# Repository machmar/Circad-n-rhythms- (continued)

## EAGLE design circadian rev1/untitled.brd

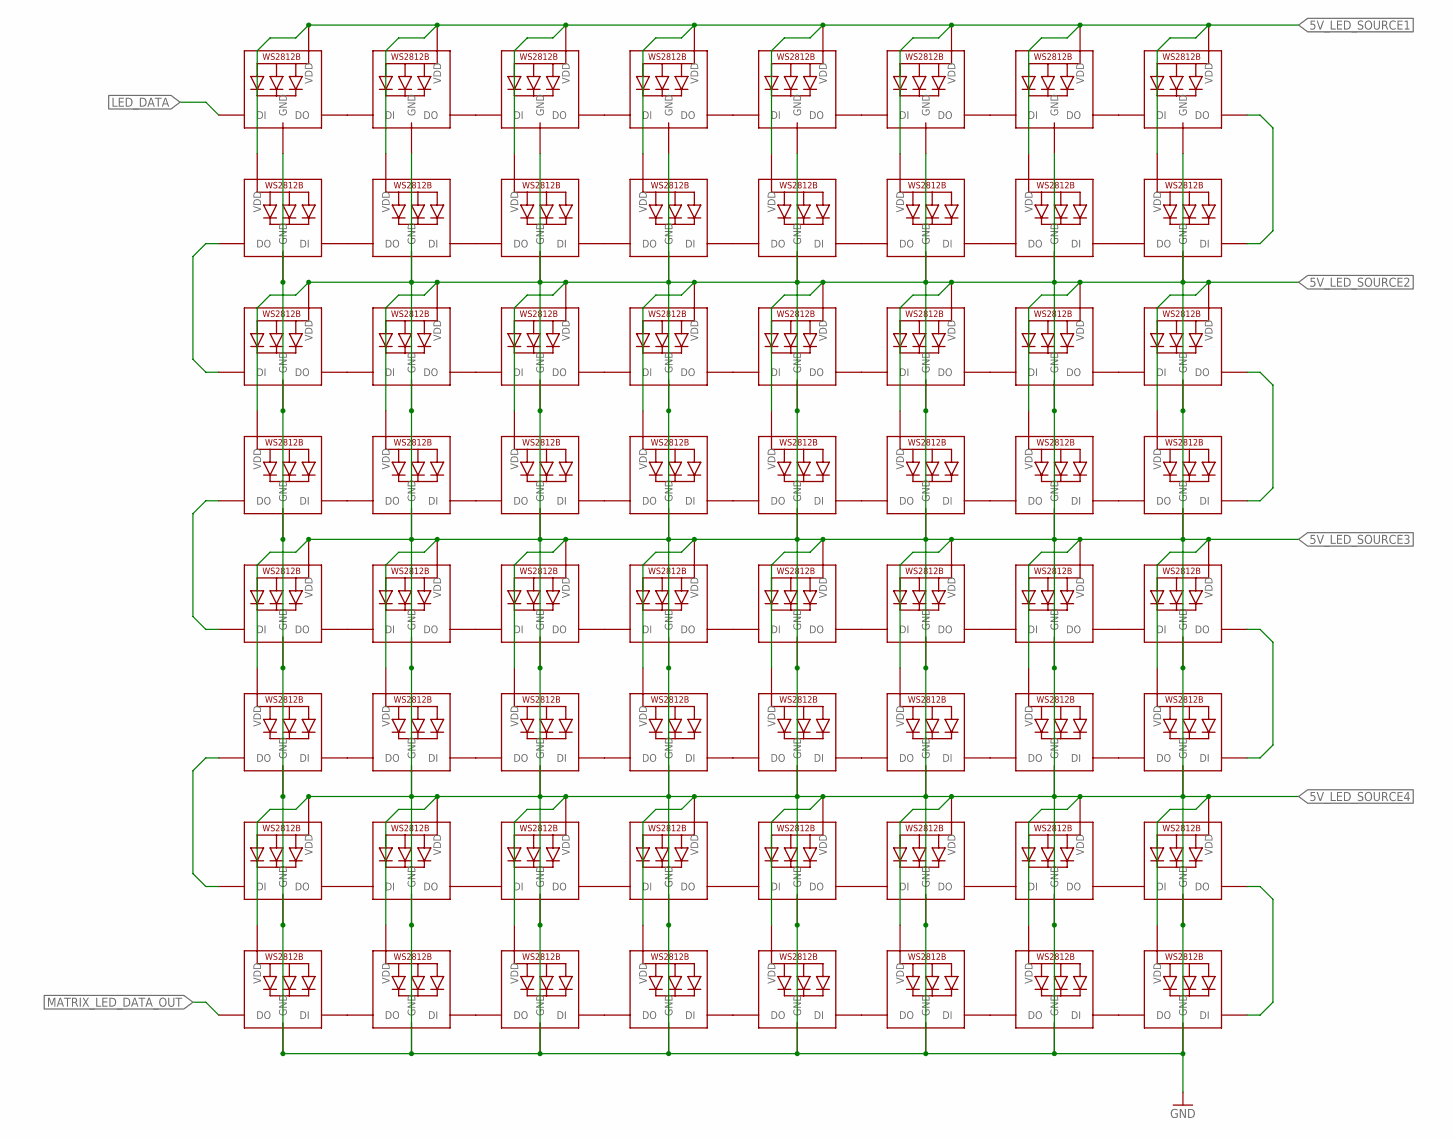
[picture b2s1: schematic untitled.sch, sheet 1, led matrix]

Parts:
LED1, LED2, LED3, LED4, LED5, LED6, LED7, LED8, LED9, LED10, LED11, LED12, LED13, LED14, LED15, LED16, LED17, LED18, LED19, LED20, LED21, LED22, LED23, LED24, LED25, LED26, LED27, LED28, LED29, LED30, LED31, LED32, LED33, LED34, LED35, LED36, LED37, LED38, LED39, LED40, LED41, LED42, LED43, LED44, LED45, LED46, LED47, LED48, LED49, LED50, LED51, LED52, LED53, LED54, LED55, LED56, LED57, LED58, LED59, LED60, LED61, LED62, LED63, LED64: WS2812B3535; LED3535

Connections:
5V_LED_SOURCE1: LED1.2 (VDD), LED2.2 (VDD), LED3.2 (VDD), LED4.2 (VDD), LED5.2 (VDD), LED6.2 (VDD), LED7.2 (VDD), LED8.2 (VDD), LED9.2 (VDD), LED10.2 (VDD), LED11.2 (VDD), LED12.2 (VDD), LED13.2 (VDD), LED14.2 (VDD), LED15.2 (VDD), LED16.2 (VDD); also elsewhere on the board
5V_LED_SOURCE2: LED17.2 (VDD), LED18.2 (VDD), LED19.2 (VDD), LED20.2 (VDD), LED21.2 (VDD), LED22.2 (VDD), LED23.2 (VDD), LED24.2 (VDD), LED25.2 (VDD), LED26.2 (VDD), LED27.2 (VDD), LED28.2 (VDD), LED29.2 (VDD), LED30.2 (VDD), LED31.2 (VDD), LED32.2 (VDD); also elsewhere on the board
5V_LED_SOURCE3: LED33.2 (VDD), LED34.2 (VDD), LED35.2 (VDD), LED36.2 (VDD), LED37.2 (VDD), LED38.2 (VDD), LED39.2 (VDD), LED40.2 (VDD), LED41.2 (VDD), LED42.2 (VDD), LED43.2 (VDD), LED44.2 (VDD), LED45.2 (VDD), LED46.2 (VDD), LED47.2 (VDD), LED48.2 (VDD); also elsewhere on the board
5V_LED_SOURCE4: LED49.2 (VDD), LED50.2 (VDD), LED51.2 (VDD), LED52.2 (VDD), LED53.2 (VDD), LED54.2 (VDD), LED55.2 (VDD), LED56.2 (VDD), LED57.2 (VDD), LED58.2 (VDD), LED59.2 (VDD), LED60.2 (VDD), LED61.2 (VDD), LED62.2 (VDD), LED63.2 (VDD), LED64.2 (VDD); also elsewhere on the board
GND: LED1.4 (GND), LED2.4 (GND), LED3.4 (GND), LED4.4 (GND), LED5.4 (GND), LED6.4 (GND), LED7.4 (GND), LED8.4 (GND), LED9.4 (GND), LED10.4 (GND), LED11.4 (GND), LED12.4 (GND), LED13.4 (GND), LED14.4 (GND), LED15.4 (GND), LED16.4 (GND), LED17.4 (GND), LED18.4 (GND), LED19.4 (GND), LED20.4 (GND), LED21.4 (GND), LED22.4 (GND), LED23.4 (GND), LED24.4 (GND), LED25.4 (GND), LED26.4 (GND), LED27.4 (GND), LED28.4 (GND), LED29.4 (GND), LED30.4 (GND), LED31.4 (GND), LED32.4 (GND), LED33.4 (GND), LED34.4 (GND), LED35.4 (GND), LED36.4 (GND), LED37.4 (GND), LED38.4 (GND), LED39.4 (GND), LED40.4 (GND), LED41.4 (GND), LED42.4 (GND), LED43.4 (GND), LED44.4 (GND), LED45.4 (GND), LED46.4 (GND), LED47.4 (GND), LED48.4 (GND), LED49.4 (GND), LED50.4 (GND), LED51.4 (GND), LED52.4 (GND), LED53.4 (GND), LED54.4 (GND), LED55.4 (GND), LED56.4 (GND), LED57.4 (GND), LED58.4 (GND), LED59.4 (GND), LED60.4 (GND), LED61.4 (GND), LED62.4 (GND), LED63.4 (GND), LED64.4 (GND); also elsewhere on the board
LED_DATA: LED1.1 (DI); also elsewhere on the board
MATRIX_LED_DATA_OUT: LED57.3 (DO); also elsewhere on the board
unnamed: LED9.1 (DI), LED10.3 (DO)
unnamed: LED10.1 (DI), LED11.3 (DO)
unnamed: LED11.1 (DI), LED12.3 (DO)
unnamed: LED12.1 (DI), LED13.3 (DO)
unnamed: LED13.1 (DI), LED14.3 (DO)
unnamed: LED14.1 (DI), LED15.3 (DO)
unnamed: LED15.1 (DI), LED16.3 (DO)
unnamed: LED25.1 (DI), LED26.3 (DO)
unnamed: LED26.1 (DI), LED27.3 (DO)
unnamed: LED27.1 (DI), LED28.3 (DO)
unnamed: LED28.1 (DI), LED29.3 (DO)
unnamed: LED29.1 (DI), LED30.3 (DO)
unnamed: LED30.1 (DI), LED31.3 (DO)
unnamed: LED31.1 (DI), LED32.3 (DO)
unnamed: LED41.1 (DI), LED42.3 (DO)
unnamed: LED42.1 (DI), LED43.3 (DO)
unnamed: LED43.1 (DI), LED44.3 (DO)
unnamed: LED44.1 (DI), LED45.3 (DO)
unnamed: LED45.1 (DI), LED46.3 (DO)
unnamed: LED46.1 (DI), LED47.3 (DO)
unnamed: LED47.1 (DI), LED48.3 (DO)
unnamed: LED1.3 (DO), LED2.1 (DI)
unnamed: LED2.3 (DO), LED3.1 (DI)
unnamed: LED3.3 (DO), LED4.1 (DI)
unnamed: LED4.3 (DO), LED5.1 (DI)
unnamed: LED5.3 (DO), LED6.1 (DI)
unnamed: LED6.3 (DO), LED7.1 (DI)
unnamed: LED7.3 (DO), LED8.1 (DI)
unnamed: LED57.1 (DI), LED58.3 (DO)
unnamed: LED24.3 (DO), LED32.1 (DI)
unnamed: LED40.3 (DO), LED48.1 (DI)
unnamed: LED56.3 (DO), LED64.1 (DI)
unnamed: LED41.3 (DO), LED49.1 (DI)
unnamed: LED25.3 (DO), LED33.1 (DI)
unnamed: LED9.3 (DO), LED17.1 (DI)
unnamed: LED58.1 (DI), LED59.3 (DO)
unnamed: LED59.1 (DI), LED60.3 (DO)
unnamed: LED60.1 (DI), LED61.3 (DO)
unnamed: LED61.1 (DI), LED62.3 (DO)
unnamed: LED62.1 (DI), LED63.3 (DO)
unnamed: LED63.1 (DI), LED64.3 (DO)
unnamed: LED17.3 (DO), LED18.1 (DI)
unnamed: LED18.3 (DO), LED19.1 (DI)
unnamed: LED19.3 (DO), LED20.1 (DI)
unnamed: LED20.3 (DO), LED21.1 (DI)
unnamed: LED21.3 (DO), LED22.1 (DI)
unnamed: LED22.3 (DO), LED23.1 (DI)
unnamed: LED23.3 (DO), LED24.1 (DI)
unnamed: LED33.3 (DO), LED34.1 (DI)
unnamed: LED34.3 (DO), LED35.1 (DI)
unnamed: LED35.3 (DO), LED36.1 (DI)
unnamed: LED36.3 (DO), LED37.1 (DI)
unnamed: LED37.3 (DO), LED38.1 (DI)
unnamed: LED38.3 (DO), LED39.1 (DI)
unnamed: LED39.3 (DO), LED40.1 (DI)
unnamed: LED49.3 (DO), LED50.1 (DI)
unnamed: LED50.3 (DO), LED51.1 (DI)
unnamed: LED51.3 (DO), LED52.1 (DI)
unnamed: LED52.3 (DO), LED53.1 (DI)
unnamed: LED53.3 (DO), LED54.1 (DI)
unnamed: LED54.3 (DO), LED55.1 (DI)
unnamed: LED55.3 (DO), LED56.1 (DI)
unnamed: LED8.3 (DO), LED16.1 (DI)

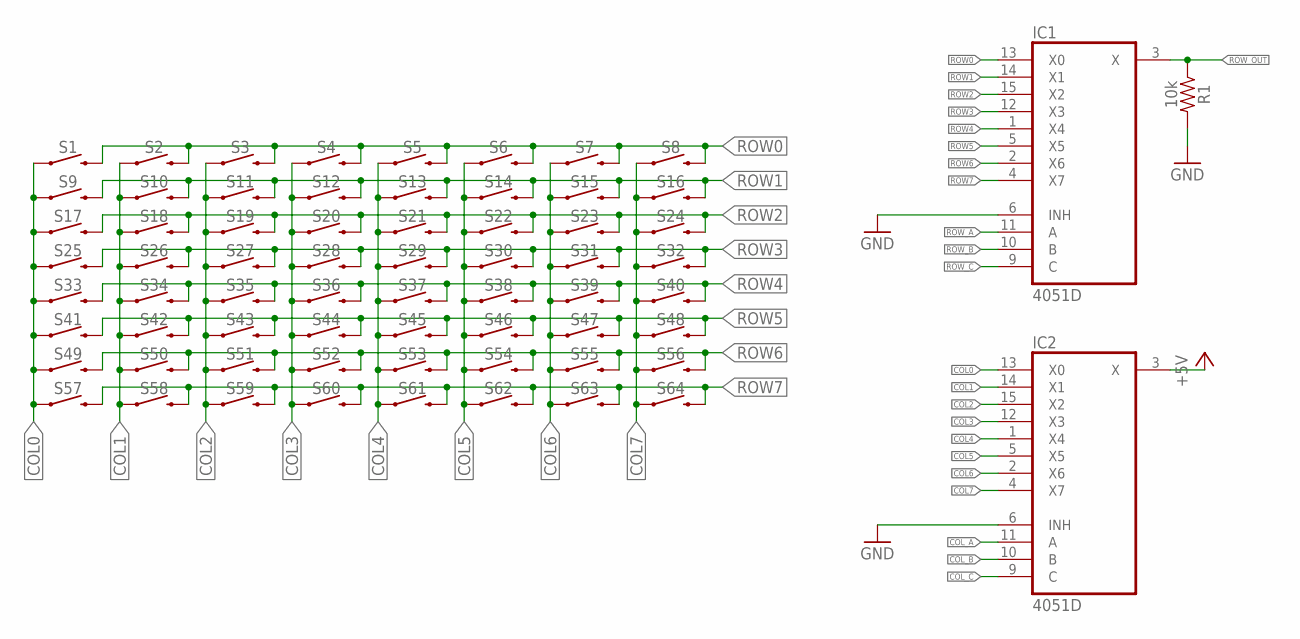
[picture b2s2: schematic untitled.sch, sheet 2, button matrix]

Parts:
IC1, IC2: 4051D; SO16
R1: 10k; 0603
S1, S2, S3, S4, S5, S6, S7, S8, S9, S10, S11, S12, S13, S14, S15, S16, S17, S18, S19, S20, S21, S22, S23, S24, S25, S26, S27, S28, S29, S30, S31, S32, S33, S34, S35, S36, S37, S38, S39, S40, S41, S42, S43, S44, S45, S46, S47, S48, S49, S50, S51, S52, S53, S54, S55, S56, S57, S58, S59, S60, S61, S62, S63, S64: MOMENTARY-SWITCH-SPST-SMD-6.0X3.5MM; TACTILE_SWITCH_SMD_6.0X3.5MM

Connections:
+5V: IC2.3 (X); also elsewhere on the board
COL0: IC2.13 (X0), S1.1, S9.1, S17.1, S25.1, S33.1, S41.1, S49.1, S57.1
COL1: IC2.14 (X1), S2.1, S10.1, S18.1, S26.1, S34.1, S42.1, S50.1, S58.1
COL2: IC2.15 (X2), S3.1, S11.1, S19.1, S27.1, S35.1, S43.1, S51.1, S59.1
COL3: IC2.12 (X3), S4.1, S12.1, S20.1, S28.1, S36.1, S44.1, S52.1, S60.1
COL4: IC2.1 (X4), S5.1, S13.1, S21.1, S29.1, S37.1, S45.1, S53.1, S61.1
COL5: IC2.5 (X5), S6.1, S14.1, S22.1, S30.1, S38.1, S46.1, S54.1, S62.1
COL6: IC2.2 (X6), S7.1, S15.1, S23.1, S31.1, S39.1, S47.1, S55.1, S63.1
COL7: IC2.4 (X7), S8.1, S16.1, S24.1, S32.1, S40.1, S48.1, S56.1, S64.1
COL_A: IC2.11 (A); also elsewhere on the board
COL_B: IC2.10 (B); also elsewhere on the board
COL_C: IC2.9 (C); also elsewhere on the board
GND: IC1.6 (INH), IC1.8 (GND), IC2.6 (INH), IC2.8 (GND), R1.2; also elsewhere on the board
ROW0: IC1.13 (X0), S1.2, S2.2, S3.2, S4.2, S5.2, S6.2, S7.2, S8.2
ROW1: IC1.14 (X1), S9.2, S10.2, S11.2, S12.2, S13.2, S14.2, S15.2, S16.2
ROW2: IC1.15 (X2), S17.2, S18.2, S19.2, S20.2, S21.2, S22.2, S23.2, S24.2
ROW3: IC1.12 (X3), S25.2, S26.2, S27.2, S28.2, S29.2, S30.2, S31.2, S32.2
ROW4: IC1.1 (X4), S33.2, S34.2, S35.2, S36.2, S37.2, S38.2, S39.2, S40.2
ROW5: IC1.5 (X5), S41.2, S42.2, S43.2, S44.2, S45.2, S46.2, S47.2, S48.2
ROW6: IC1.2 (X6), S49.2, S50.2, S51.2, S52.2, S53.2, S54.2, S55.2, S56.2
ROW7: IC1.4 (X7), S57.2, S58.2, S59.2, S60.2, S61.2, S62.2, S63.2, S64.2
ROW_A: IC1.11 (A); also elsewhere on the board
ROW_B: IC1.10 (B); also elsewhere on the board
ROW_C: IC1.9 (C); also elsewhere on the board
ROW_OUT: IC1.3 (X), R1.1; also elsewhere on the board
VCC: IC1.16 (VCC), IC2.16 (VCC); also elsewhere on the board
VEE: IC1.7 (VEE), IC2.7 (VEE); also elsewhere on the board

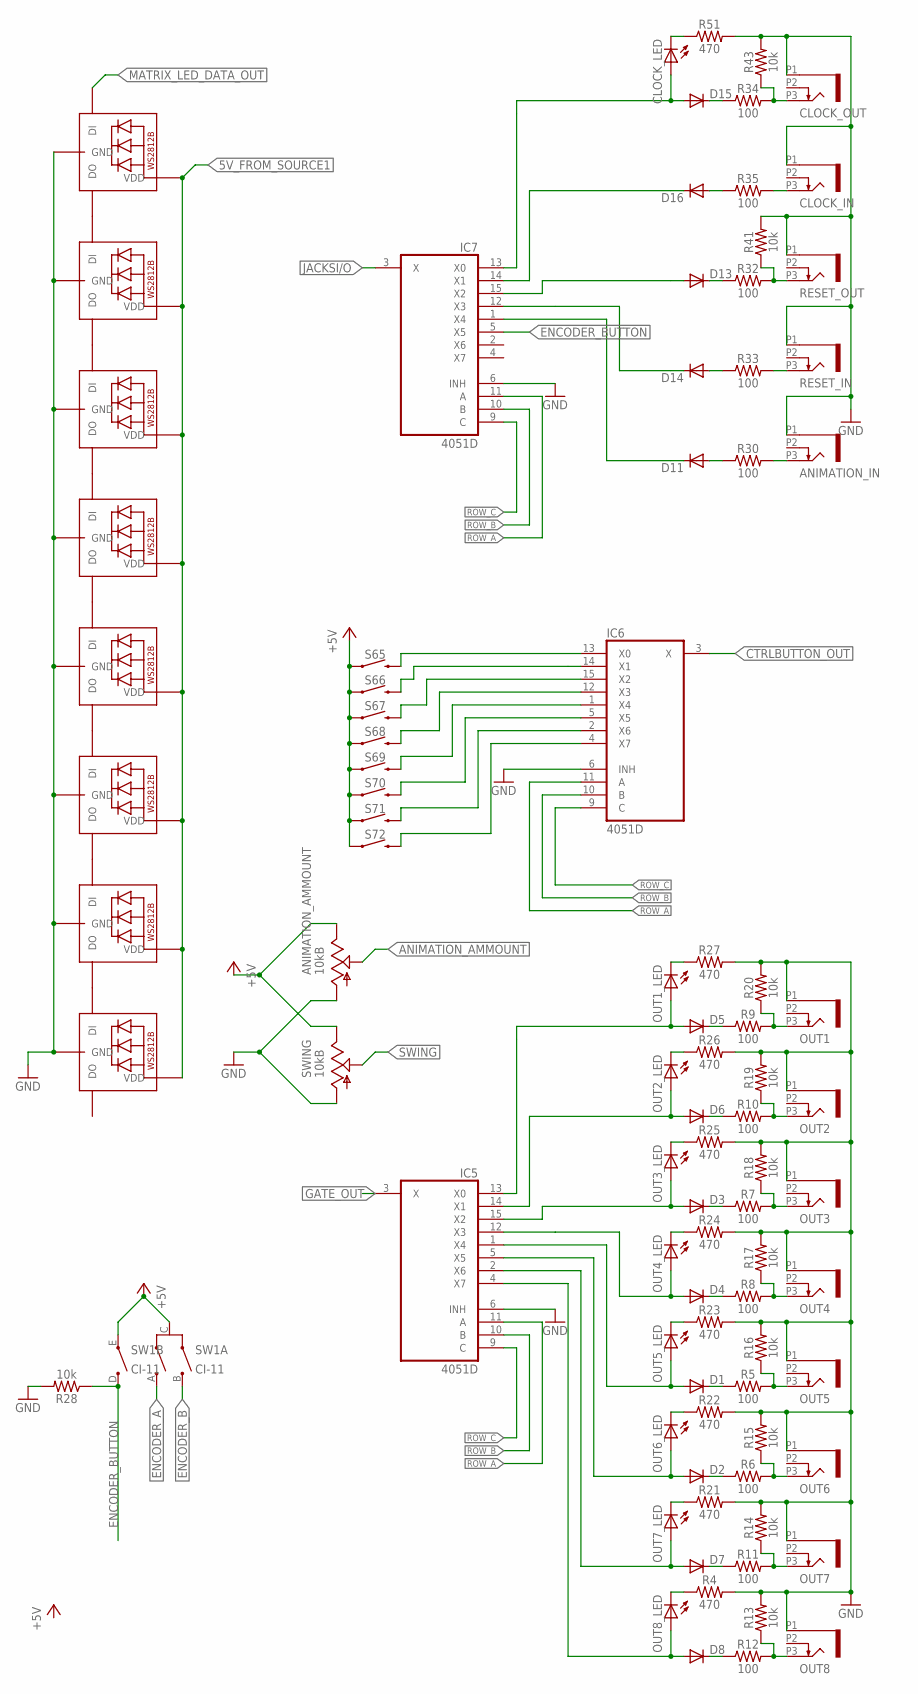
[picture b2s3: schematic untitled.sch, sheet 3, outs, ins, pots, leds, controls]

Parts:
ANIMATION_AMMOUNT: 10kB; ALPS_POT_VERTICAL
ANIMATION_IN: PJ301_THONKICONN8; WQP_PJ_301M8
CLOCK_IN: PJ301_THONKICONN1; WQP_PJ_301M1
CLOCK_LED: LED5MM
CLOCK_OUT: PJ301_THONKICONN1; WQP_PJ_301M1
D1, D2, D3, D4, D5, D6, D7, D8, D11, D13, D14, D15, D16: DIODE-DO214AC; DO214AC
IC5, IC6, IC7: 4051D; SO16
LED65, LED66, LED67, LED68, LED69, LED70, LED71, LED72: WS2812B3535; LED3535
OUT1, OUT2, OUT3, OUT4, OUT5, OUT6: PJ301_THONKICONN1; WQP_PJ_301M1
OUT1_LED, OUT2_LED, OUT3_LED, OUT4_LED, OUT5_LED, OUT6_LED, OUT7_LED, OUT8_LED: LED5MM
OUT7, OUT8: PJ301_THONKICONN8; WQP_PJ_301M8
R4, R21, R22, R23, R24, R25, R26, R27, R51: 470; 0603
R5, R6, R7, R8, R9, R10, R11, R12, R30, R32, R33, R34, R35: 100; 0603
R13, R14, R15, R16, R17, R18, R19, R20, R28, R41, R43: 10k; 0603
RESET_IN: PJ301_THONKICONN1; WQP_PJ_301M1
RESET_OUT: PJ301_THONKICONN8; WQP_PJ_301M8
S65, S66, S67, S68, S69, S70, S71, S72: MOMENTARY-SWITCH-SPST-SMD-6.0X3.5MM; TACTILE_SWITCH_SMD_6.0X3.5MM
SW1: CI-11
SWING: 10kB; ALPS_POT_VERTICAL

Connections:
5V_FROM_SOURCE1: LED65.2 (VDD), LED66.2 (VDD), LED67.2 (VDD), LED68.2 (VDD), LED69.2 (VDD), LED70.2 (VDD), LED71.2 (VDD), LED72.2 (VDD); also elsewhere on the board
+5V: ANIMATION_AMMOUNT.P$1 (E), S65.1, S66.1, S67.1, S68.1, S69.1, S70.1, S71.1, S72.1, SW1.C, SW1.E, SWING.P$1 (E); also elsewhere on the board
ANIMATION_AMMOUNT: ANIMATION_AMMOUNT.P$2 (S); also elsewhere on the board
CTRLBUTTON_OUT: IC6.3 (X); also elsewhere on the board
ENCODER_A: SW1.A; also elsewhere on the board
ENCODER_B: SW1.B; also elsewhere on the board
ENCODER_BUTTON: IC7.5 (X5), R28.1, SW1.D
GATE_OUT: IC5.3 (X); also elsewhere on the board
GND: ANIMATION_AMMOUNT.P$3 (A), ANIMATION_IN.P1 (1), CLOCK_IN.P1 (1), CLOCK_OUT.P1 (1), IC5.6 (INH), IC5.8 (GND), IC6.6 (INH), IC6.8 (GND), IC7.6 (INH), IC7.8 (GND), LED65.4 (GND), LED66.4 (GND), LED67.4 (GND), LED68.4 (GND), LED69.4 (GND), LED70.4 (GND), LED71.4 (GND), LED72.4 (GND), OUT1.P1 (1), OUT2.P1 (1), OUT3.P1 (1), OUT4.P1 (1), OUT5.P1 (1), OUT6.P1 (1), OUT7.P1 (1), OUT8.P1 (1), R4.2, R13.2, R14.2, R15.2, R16.2, R17.2, R18.2, R19.2, R20.2, R21.2, R22.2, R23.2, R24.2, R25.2, R26.2, R27.2, R28.2, R41.2, R43.2, R51.2, RESET_IN.P1 (1), RESET_OUT.P1 (1), SWING.P$3 (A); also elsewhere on the board
JACKSI/O: IC7.3 (X); also elsewhere on the board
MATRIX_LED_DATA_OUT: LED72.1 (DI); also elsewhere on the board
unnamed: D1.C, R5.1
unnamed: D2.C, R6.1
unnamed: OUT6.P3 (3), R6.2, R15.1
unnamed: OUT5.P3 (3), R5.2, R16.1
unnamed: D3.C, R7.1
unnamed: D4.C, R8.1
unnamed: D7.C, R11.1
unnamed: D8.C, R12.1
unnamed: OUT8.P3 (3), R12.2, R13.1
unnamed: OUT7.P3 (3), R11.2, R14.1
unnamed: OUT4.P3 (3), R8.2, R17.1
unnamed: OUT3.P3 (3), R7.2, R18.1
unnamed: D5.C, R9.1
unnamed: D6.C, R10.1
unnamed: OUT2.P3 (3), R10.2, R19.1
unnamed: OUT1.P3 (3), R9.2, R20.1
unnamed: D5.A, IC5.13 (X0), OUT1_LED.A
unnamed: D6.A, IC5.14 (X1), OUT2_LED.A
unnamed: D3.A, IC5.15 (X2), OUT3_LED.A
unnamed: D4.A, IC5.12 (X3), OUT4_LED.A
unnamed: D1.A, IC5.1 (X4), OUT5_LED.A
unnamed: D2.A, IC5.5 (X5), OUT6_LED.A
unnamed: D7.A, IC5.2 (X6), OUT7_LED.A
unnamed: D8.A, IC5.4 (X7), OUT8_LED.A
unnamed: LED65.3 (DO), LED66.1 (DI)
unnamed: LED65.1 (DI), LED70.3 (DO)
unnamed: LED66.3 (DO), LED67.1 (DI)
unnamed: LED67.3 (DO), LED68.1 (DI)
unnamed: LED68.3 (DO), LED69.1 (DI)
unnamed: LED69.3 (DO), LED71.1 (DI)
unnamed: LED70.1 (DI), LED72.3 (DO)
unnamed: OUT1_LED.K (C), R27.1
unnamed: OUT2_LED.K (C), R26.1
unnamed: OUT3_LED.K (C), R25.1
unnamed: OUT4_LED.K (C), R24.1
unnamed: OUT5_LED.K (C), R23.1
unnamed: OUT6_LED.K (C), R22.1
unnamed: OUT7_LED.K (C), R21.1
unnamed: OUT8_LED.K (C), R4.1
unnamed: D16.A, R35.1
unnamed: D14.A, R33.1
unnamed: D11.A, R30.1
unnamed: ANIMATION_IN.P3 (3), R30.2
unnamed: D13.C, R32.1
unnamed: R33.2, RESET_IN.P3 (3)
unnamed: R32.2, R41.1, RESET_OUT.P3 (3)
unnamed: D15.C, R34.1
unnamed: CLOCK_IN.P3 (3), R35.2
unnamed: CLOCK_OUT.P3 (3), R34.2, R43.1
unnamed: CLOCK_LED.A, D15.A, IC7.13 (X0)
unnamed: D16.C, IC7.14 (X1)
unnamed: D13.A, IC7.15 (X2)
unnamed: D14.C, IC7.12 (X3)
unnamed: D11.C, IC7.1 (X4)
unnamed: CLOCK_LED.K (C), R51.1
ROW8: IC6.13 (X0), S65.2
ROW9: IC6.14 (X1), S66.2
ROW10: IC6.15 (X2), S67.2
ROW11: IC6.12 (X3), S68.2
ROW12: IC6.1 (X4), S69.2
ROW13: IC6.5 (X5), S70.2
ROW14: IC6.2 (X6), S71.2
ROW15: IC6.4 (X7), S72.2
ROW_A: IC5.11 (A), IC6.11 (A), IC7.11 (A); also elsewhere on the board
ROW_B: IC5.10 (B), IC6.10 (B), IC7.10 (B); also elsewhere on the board
ROW_C: IC5.9 (C), IC6.9 (C), IC7.9 (C); also elsewhere on the board
SWING: SWING.P$2 (S); also elsewhere on the board
VCC: IC5.16 (VCC), IC6.16 (VCC), IC7.16 (VCC); also elsewhere on the board
VEE: IC5.7 (VEE), IC6.7 (VEE), IC7.7 (VEE); also elsewhere on the board

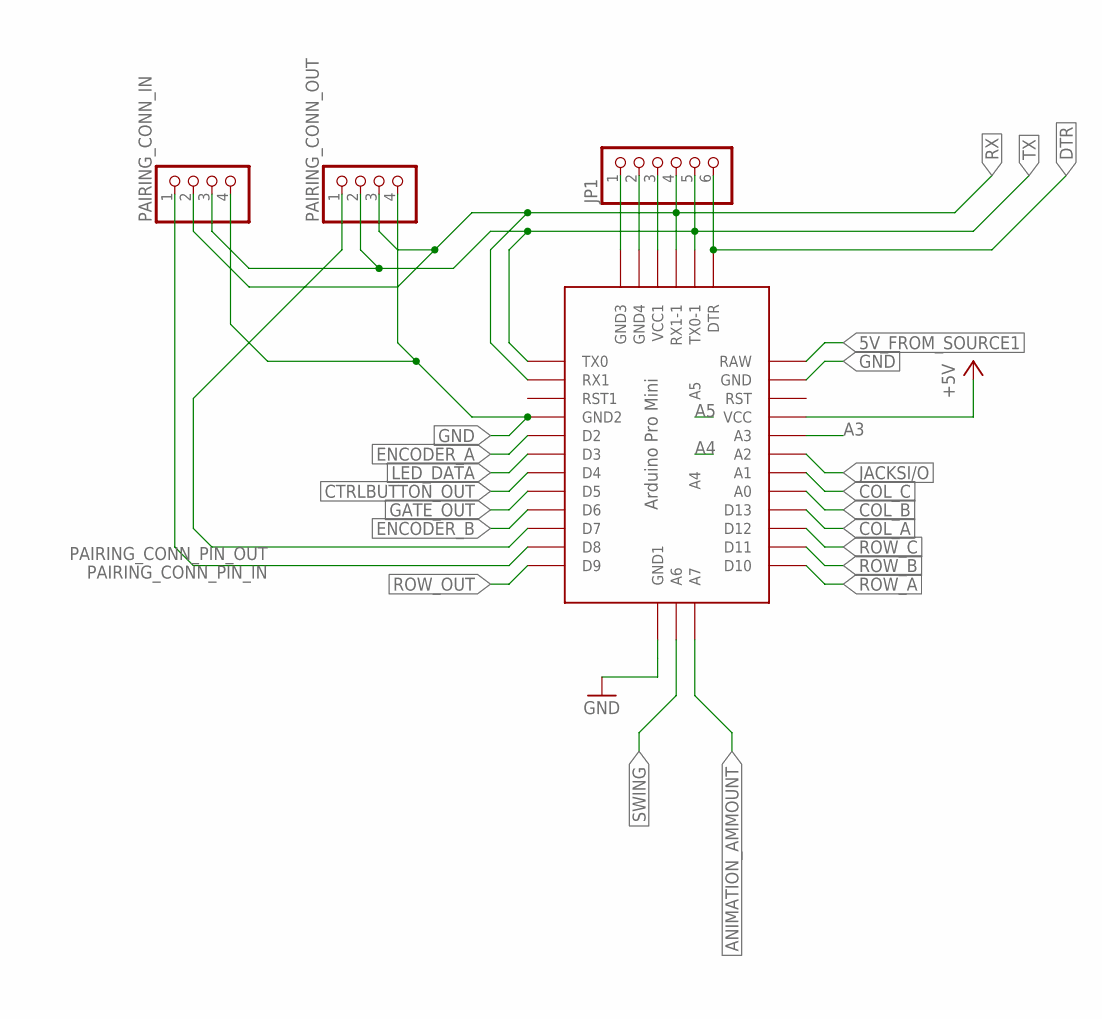
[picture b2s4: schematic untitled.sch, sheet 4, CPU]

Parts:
JP1: PINHD-1X6; 1X06
PAIRING_CONN_IN: PINHD-1X4; 1X04
PAIRING_CONN_OUT: PINHD-1X4; 1X04
U$1: ABK-PRO-MINI

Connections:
5V_FROM_SOURCE1: U$1.RAW; also elsewhere on the board
+5V: JP1.3, U$1.VCC, U$1.VCC1; also elsewhere on the board
A3: U$1.A3
A4: U$1.A4
A5: U$1.A5
ANIMATION_AMMOUNT: U$1.A7; also elsewhere on the board
COL_A: U$1.D13; also elsewhere on the board
COL_B: U$1.A0; also elsewhere on the board
COL_C: U$1.A1; also elsewhere on the board
CTRLBUTTON_OUT: U$1.D4; also elsewhere on the board
DTR: JP1.6, U$1.DTR; also elsewhere on the board
ENCODER_A: U$1.D2; also elsewhere on the board
ENCODER_B: U$1.D6; also elsewhere on the board
GATE_OUT: U$1.D5; also elsewhere on the board
GND: JP1.1, JP1.2, PAIRING_CONN_IN.4, PAIRING_CONN_OUT.4, U$1.GND, U$1.GND1 (GND2), U$1.GND2 (GND3), U$1.GND3 (GND4), U$1.GND4 (GND1); also elsewhere on the board
JACKSI/O: U$1.A2; also elsewhere on the board
LED_DATA: U$1.D3; also elsewhere on the board
PAIRING_CONN_PIN_IN: PAIRING_CONN_IN.1, U$1.D8
PAIRING_CONN_PIN_OUT: PAIRING_CONN_OUT.1, U$1.D7
ROW_A: U$1.D10; also elsewhere on the board
ROW_B: U$1.D11; also elsewhere on the board
ROW_C: U$1.D12; also elsewhere on the board
ROW_OUT: U$1.D9; also elsewhere on the board
RX: JP1.4, PAIRING_CONN_IN.2, PAIRING_CONN_OUT.3, U$1.RX1, U$1.RX1-1; also elsewhere on the board
SWING: U$1.A6; also elsewhere on the board
TX: JP1.5, PAIRING_CONN_IN.3, PAIRING_CONN_OUT.2, U$1.TX0, U$1.TX0-1; also elsewhere on the board

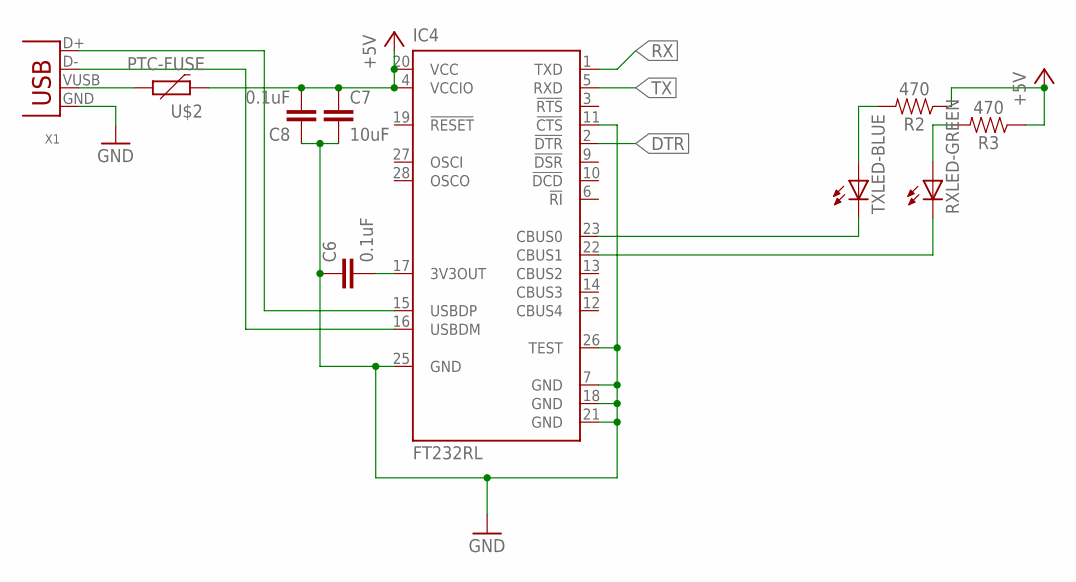
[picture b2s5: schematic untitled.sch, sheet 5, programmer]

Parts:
C6, C8: 0.1uF; 0603
C7: 10uF; 0603
IC4: FT232RL; SSOP28
R2, R3: 470; 0603
RXLED-GREEN: LEDCHIP-LED0603; CHIP-LED0603
TXLED-BLUE: LEDCHIP-LED0603; CHIP-LED0603
U$2: PTC-FUSE; 1206
X1: USB-B-S; USB-B-SMT

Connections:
+5V: C7.1, C8.2, IC4.4 (VCCIO), IC4.20 (VCC), R2.1, R3.1, U$2.1; also elsewhere on the board
DTR: IC4.2 (!DTR); also elsewhere on the board
GND: C6.1, C7.2, C8.1, IC4.7 (GND), IC4.11 (!CTS), IC4.18 (GND), IC4.21 (GND), IC4.25 (GND), IC4.26 (TEST), X1.GND; also elsewhere on the board
unnamed: R2.2, TXLED-BLUE.A
unnamed: R3.2, RXLED-GREEN.A
unnamed: U$2.2, X1.VUSB (VBUS)
unnamed: IC4.23 (CBUS0), TXLED-BLUE.C
unnamed: IC4.22 (CBUS1), RXLED-GREEN.C
unnamed: IC4.15 (USBDP), X1.D+
unnamed: IC4.16 (USBDM), X1.D-
unnamed: C6.2, IC4.17 (3V3OUT)
RX: IC4.1 (TXD); also elsewhere on the board
TX: IC4.5 (RXD); also elsewhere on the board

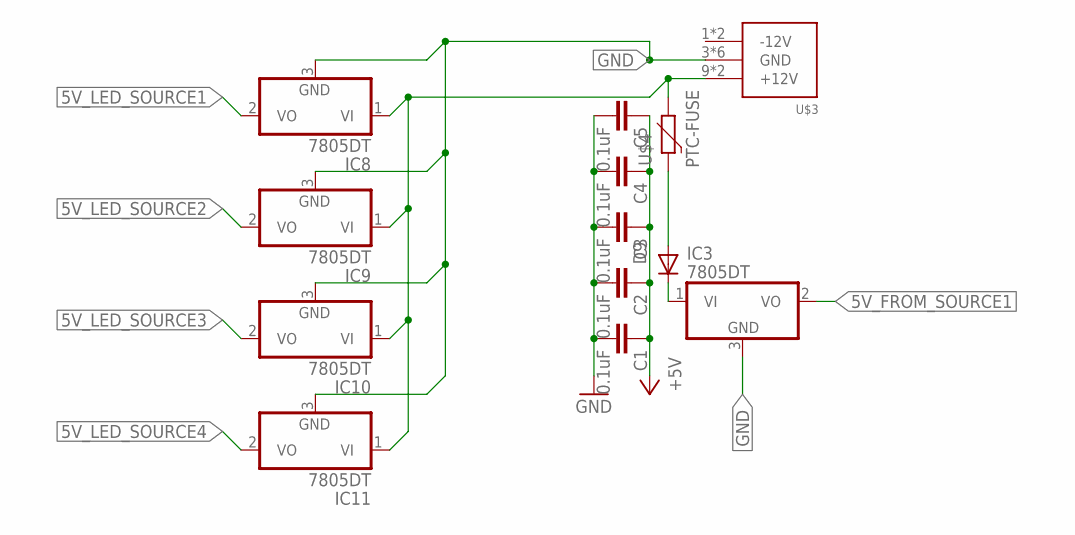
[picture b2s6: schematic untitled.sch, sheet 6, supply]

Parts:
C1, C2, C3, C4, C5: 0.1uF; 0603
D9: 1N5819HW; SOD123
IC3, IC8, IC9, IC10, IC11: 7805DT; TO252
U$3: POWER_SIMPLE10; POWER_10
U$4: PTC-FUSE; 1206

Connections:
5V_FROM_SOURCE1: IC3.2 (VO); also elsewhere on the board
5V_LED_SOURCE1: IC8.2 (VO); also elsewhere on the board
5V_LED_SOURCE2: IC9.2 (VO); also elsewhere on the board
5V_LED_SOURCE3: IC10.2 (VO); also elsewhere on the board
5V_LED_SOURCE4: IC11.2 (VO); also elsewhere on the board
+5V: C1.1, C2.1, C3.1, C4.1, C5.1; also elsewhere on the board
GND: C1.2, C2.2, C3.2, C4.2, C5.2, IC3.3 (GND), IC8.3 (GND), IC9.3 (GND), IC10.3 (GND), IC11.3 (GND), U$3.3 (GND), U$3.4 (GND), U$3.5 (GND), U$3.6 (GND), U$3.7 (GND), U$3.8 (GND); also elsewhere on the board
unnamed: IC8.1 (VI), IC9.1 (VI), IC10.1 (VI), IC11.1 (VI), U$3.9 (+12V), U$3.10 (+12V), U$4.2
unnamed: D9.A, U$4.1
unnamed: D9.C, IC3.1 (VI)

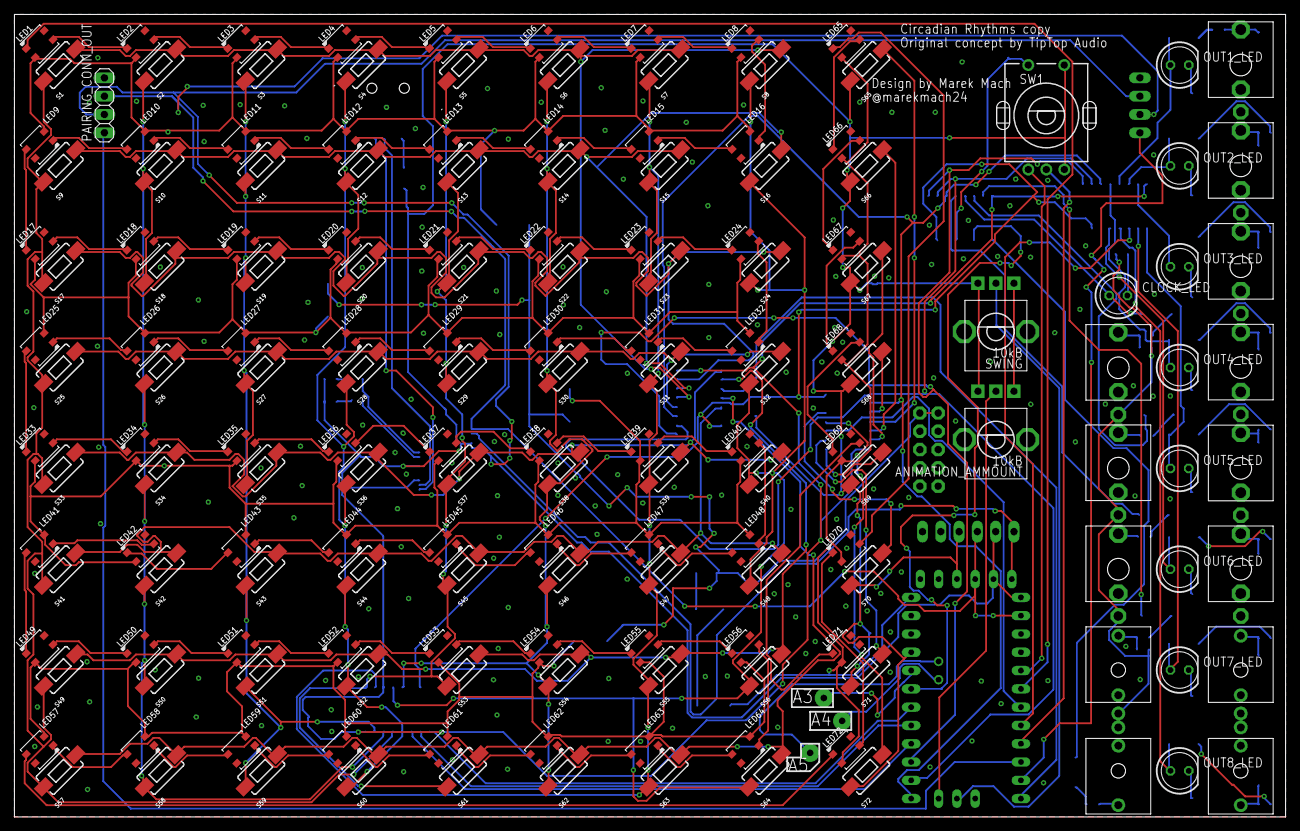
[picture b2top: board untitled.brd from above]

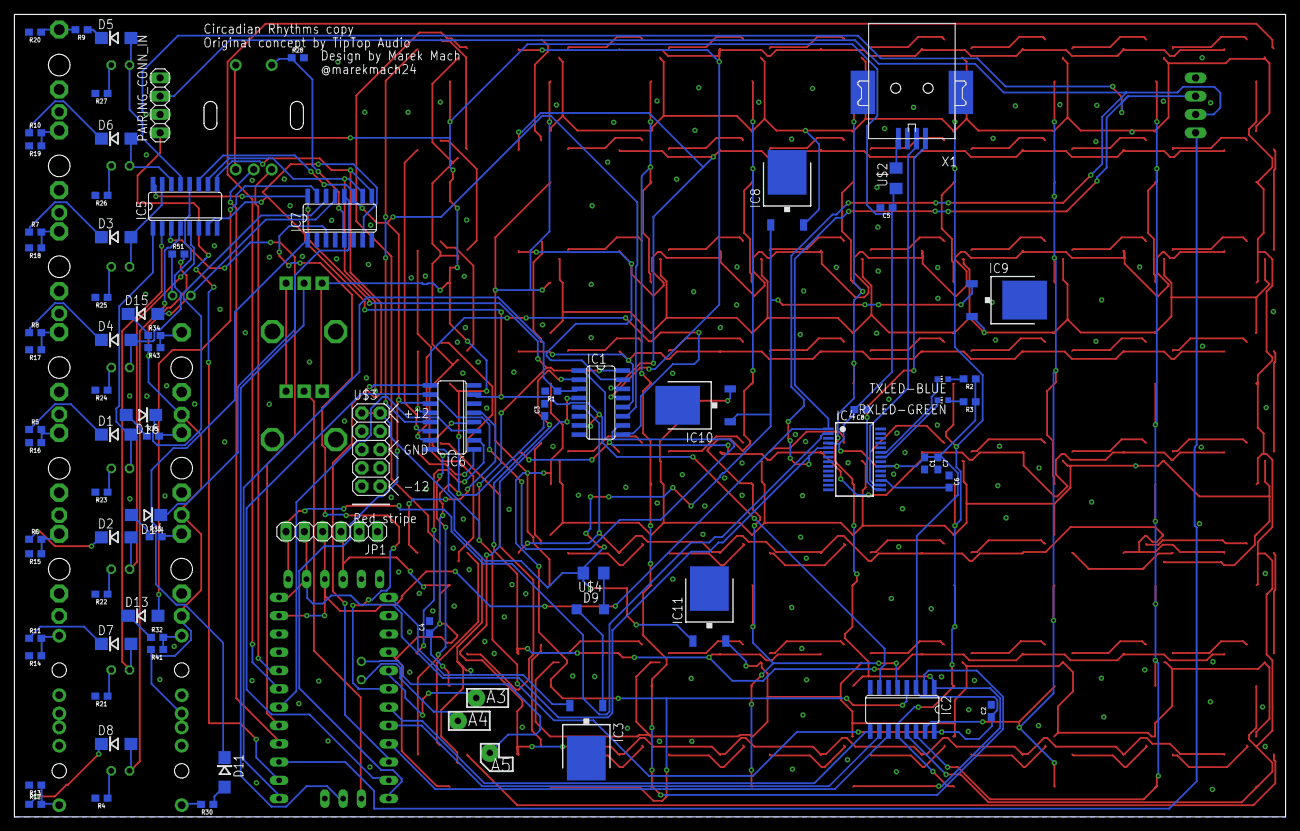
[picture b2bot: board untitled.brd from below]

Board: 2 copper layers, 176.5 x 111.4 mm, 248 parts (78 on the bottom side), 184 nets.

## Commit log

2018-12-15 The pcb and schematic
2019-07-30 it works now
    kinda
2019-07-30 code works now
    use the rev2.2
2019-07-30 code now works
2019-07-30 updated library description
2019-08-26 mostly bug fixes
2019-09-08 pcb 2.0 finished
2019-09-22 added BOM
2019-09-22 updated to the new pcb
2020-01-01 the code now fully works
2020-02-18 BOM is fixed, Im sorry for that scam link.
    Hopefully nobody bought that arduino pro mini.
2020-07-06 added wiki
2020-07-07 added debug files for easier fixing
2020-07-07 Added PCB and Schematic images
2020-07-07 fixed a mistake
2020-08-26 The long awaited 2.5 update has been initiated.
2020-08-26 small description
2020-08-26 added compiled hex file
2020-08-29 Rename reademe.md to README.md
2020-10-31 Fixed macro precalculation
2020-12-09 moved wiki images from imgur to here
2020-12-09 dumb formating stuff bruh
2021-01-04 added a booting gif
2021-01-05 added the video
2021-09-23 Fixed the BOM
2021-09-24 added rev 2.5.1
2023-11-24 fixed mistakes on the pcb
    There are no pictures, no BOM and no additional files, this is really just a hotfix
2023-11-24 Rewritten RADME
2023-11-24 Added a readme to 2.5.1 code folder
2023-11-24 Update README.md for the 2.5.1 code
2023-11-27 Added and fixed a BOM for 2.1
2023-12-16 Added a comment fo fix confusion
2023-12-16 Fixed wrong LED type causing confusion
